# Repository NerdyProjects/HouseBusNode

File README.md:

# Hausbus Spielerei

## Short introduction

This repository holds hardware and software design for a work in progress house bus system.
It operates using a 4-wire bus using the CAN bus as well as supply of ~10 - 20 V.
It should provide a base for very simple nodes (e.g. sensors, digital actors) as well as more complex nodes (e.g. a heating system controller).

## Background

The system design started in November 2017 when the need of a better heating system controller arose in a housing project in Wurzen, Germany.
The gas heating system, a well overpowered Viessmann Atola controlled by a Viessmann Trimatik MC should be better controlled in light load conditions with options to get it better tuned to the actual needs.
A good heating system needs to be remote controllable as well as take a lot of different control inputs, in best case from every room as well as every radiator and maybe even some valves in between.

Additionally, it is nice to gather statistics about used gas, electricity and water.

When such a system is in place already, it would be great to combine it with other actors and sensors around the house: Doorbell, switches, PIR sensors, dimming of lights (without having to use expensive dimmers or even without standing up from your desk).

## Design implications

The design is driven by a mind that likes to play around with technology, gather statistics and try to optimize the world around.
The design is not meant to be used for things that require absolute reliability or fool-saveness.
The design is not meant to be used in applications or environment where security is needed.
The communication between the nodes happen without any security layer: Every node is able to set any value in any other node, so can everybody tapping into the bus wire.

# Hardware description

## PCB Errata

## Mini-PCB

* Triac T1/T2 (Pin 1/2) need to be exchanged. Easiest to be done by soldering Triac backwards just with Pin 1 and 2 and using a wire for Pin 3.

## Microcontroller

The microcontroller in use is the STM32F072RBT6. It is powered by an ARM Cortex-M0 core with 128 kBytes of flash memory and 16 kBytes of SRAM data memory.

### Compatible boards/projects

There is a list of boards using the same controller.
Because of the broad availability and use of these boards, they might be worth a look for application examples (be it hardware or software).

* STM32F072 Discovery Kit
* STM32 Nucleo-64 / Nucleo-F072RB (Arduino like development board)

## BUS

The CAN-Bus is not meant to operate with long stub lines - but using slew rate control, it is safe to do so.
Following CAN physical layer requirements (TI SLLA270, 01/2008), the maximum stub length should be less than 1/3rd of the critical length, which equals the down-and-back delay of the transition time, which is the longer of the rise or fall times:

| HVD230 Rs | Tplh | Tphl | 1/3 of critical length | max. length @ 250 kBaud | max. length @ 125 kBaud |
| --------- | ---- | ---- | ---------------------- | ----------------------- | ----------------------- |
| 0         | 35 ns| 70 ns | 2.3 m (1.1 m)         | ~280 m |
| 10k       | 65 ns| 130 ns | 4.3 m (2.1 m)        | ~282 m |
| 100k      | 500 ns| 870 ns | 29 m (16.6 m) | ~208 m |

The max. length is calculated using the HVD230 given tp of ~37 ns, the comparator delay inside the processor is estimated with 10 ns.
The calculation shows, that the effect of slew rate control on bus length is minimal for these speeds.
At a higher speed, the transition delay inside the driver takes up bigger parts of the available time window, which is ~3 us for 250 kBaud.
Also, it is not exactly clear to me why the speed does not matter when calculating the stub lengths, but the given results clearly show, that 100k slew rate control and a 250 kBaud bus is appropriate for usage in a house.
For a normal sized living house, the bus should be fed through each flats hallway to allow each rooms' connection with stubs.
For houses like the housing project where this is designed for, this leads to a bus length of approximately 120m:
Both ends "stub" 30m each, 2 times 3 floors with 3.5 m height (connection just through stubs, as all points are reachable within 30m), 2 times basement to pass to the next building (15m), which sums up to 30+30+2\*3\*3.5+15+15 = 111m

## Power

Each bus node has an on-board step down converter to convert the bus voltage (because of the availabiliy of cheap step downs <24 V) to 3.3 V for the circuit.
Some applications might use the bus power directly, when exact voltage does not matter and current is limited (so the bus is not powered off).
The network should be usable with ~50 nodes that can be power-fed at multiple times in the bus.

The bus cable resistance following the above approximation (120m) and taking 0.4mm/0.13mm² cable (AWG26) as a worst case candidate comes down to ~30 ohms.
Taking a worst case, default active operational current of 50 mA @ 3.3V for 50 nodes (~8 W), as well as a supply of 18 V already results in a current consumption of 450 mA, which would be too big for the given cabling.
Due to this, power consumption of nodes should be kept in mind when deploying them.

A node that is close to a powerful bus power feed can easily use the bus power to drive lighting or a doorbell with 20 W.
It is left to the deployer of the bus system to ensure that the bus voltage drop is taken into account when deploying powerful nodes.

## Board pin mapping (Board: Hausspielerei 11/2017)

Please always consider the schematics for details.
Still, the following table describes the available connectors, suggested use cases and possible use cases.

### Analog IO

Analog pins on this board are named with their corresponding usage on the Viessmann Trimatik-MC.
All of the pins in the list feature strong pullup resistors, that are all switched by /PA0 (Q1) to AVCC (3,3V)

| pin name | controller pin | available hardware | possible alternative functions |
| -------- | -------------- | ------------------ | ------------------------------ |
| IN\_ATS  | PA1            | series 0805, 2x 0805 to GND | USART2\_RTS / RS422 DE / RS485 DE, USART4\_RX |
| IN\_KTS  | PA2            | 0805 to GND | USART2\_TX / RS422 TX / RS485 TX, COMP1\_INP, COMP2\_INM, COMP2\_OUT |
| IN\_VTS  | PA3            | 0805 to GND | USART2\_RX / RS422 RX / RS485 RX, COMP2\_INP |
| IN\_STS  | PA4            | 0805 to GND | COMP2\_INM, COMP1\_INM, DAC_OUT1 |
| IN\_FB1  | PA5            | 0805 to GND | COMP1\_INM, COMP2\_INM, DAC_OUT2, SPI1\_SCK |  
| IN\_FB2  | PA6            | 0805 to GND | COMP1\_OUT, SPI1\_MISO |
| LED_A    | PA7            | series 0805 | COMP2\_OUT, SPI1\_MOSI |

### Connectors

| Connector  | Pins                           | controller pins | primary purpose | alternative purposes | conflicting with |
| ---------- | -----------------------------  | --------------- | --------------- | -------------------- | ---------------  |
| J12, J13   | VCC GND CANH CANL              |                 | Power (5-24V), bus + passthrough |     | No conflicts |
| SMPS (J3)  | NC Vin(J12/13 Vcc) GND 3,3V    |                 | SMPS module for 3,3V power supply |    | No conflicts |
| RS485 (J17)| GND A B 3,3V                   | PA1, PA2, PA3   | RS485/RS422 connection to sub boards | By bridging appropriate Pins in U1, it can be used as USART2 TX/RX/RTS or Analog inputs | DE: J9 / IN\_ATS |
| J9         | IN\_FB1 3,3V GND IN\_ATS        | PA5, PA1        | digital/analog input for hall sensor module | | IN\_ATS: RS485 DE |
| D1 (LED A) | GND LED\_A                     | PA7             | General purpose LED | IO, Analog comparator output, SPI MOSI | No conflicts |
| J16 (230V) | SW2-A SW2-B SW1-A SW1-B        | PB0 (SW2), PB11 (SW1) | Opto triac + triac controlled power switch for 230V AC | Switching, Dimming, GPIO | No conflicts |
| J6 (DIN4..1) | DIN4 DIN3 DIN2 DIN1          | PB1 PB2 PB10 PF1 | GPIO | DIN4: Analog In | No conflicts |
| D2 (LED B) | GND LED\_B                     | PA15            | General purpose LED | IO, USART2\_RX | No conflicts |
| J5 (GND)   | GND GND GND GND                |                 | | |
| J14        | SW3 GND SW4 GND                | PA8 PB3         | Open drain load switch, TIM1\_CH1, TIM2\_CH2 | 4: SPI1\_SCK | No conflicts |
| J15        | SW1 GND SW2 GND                | PB4 PB5         | Open drain load switch, TIM3\_CH1, TIM3\_CH2 | SPI1\_MISO SPI1\_MOSI | No conflicts |
| J10 (I2C)  | 3,3V GND SCL SDA               | PB6 PB7         | I2C | USART1\_TX, USART1\_RX | Shared I2C bus with J8, EEPROM |
| J8 (I2C)   | 3,3V GND SCL SDA               | PB6 PB7         | I2C | USART1\_TX, USART1\_RX | Shared I2C bus with J10, EEPROM |
| J4 (BOOT)  | GND BOOT 3,3V                  | BOOT            | bootmode selection (1-2: FLASH, 2-3: system rom bootloader) | | |
| J7 (SWD)   | SWDIO SWDCLK GND               | PA13 PA14       | SWD debug / programming connector | | No conflicts |
| J11 (USB)  | DP DM GND                      | PA12 PA11       | USB connection | COMP2\_OUT COMP1\_OUT | No conflicts |
| J18 (UART) | TX RX GND                      | PA9 PA10        | USART1\_TX USART1\_RX | TIM1\_CH2 TIM1\_CH3 | No conflicts |
| J1/J2      | see schematics                 | see schematics  | Viessmann Trimatik MC X1 | use signals individually, see schematics |

A lot of the connectors share the same physical pins.
Especially the Trimatik-MC connector shares pins with almost all other connectors, so it is not explicitly listed in the above table.
Some functionality of the Trimatik-MC might be disabled by cutting pins (or checking for electrical compatibility) - otherwise the following connectors are conflict free here as well:

  * SWD
  * I2C
  * CAN
  * J15 / Open drain switches 1, 2

When keeping minimum Trimatik-MC controller features, following connectors can never be used:
  
  * USB
  * J17 RS422/RS485
  * 230V SW1 (only by cutting J1 Pin12)

Please have a look at the schematics when wanting to use conflicting connectors at the same time, there might be options :-)

# Software description

## USB CAN Adapter firmware
The hardware should be compatible to the [CandleLight](https://github.com/HubertD/candleLight) project, so you can just use the [CandleLight Firmware](https://github.com/HubertD/candleLight_fw).
Just one change: This hardware does not supply any external oscillator, so the firmware might need to be adapted.
This firmware has not been tested.

## Ideas

## RTOS
The simplicity of each individual node does not require an operating system.
For simplicity, ease of use and improval of robustness, a simple task scheduler is highly recommended.

[ChibiOs](http://www.chibios.org) provides a simple, high performance, low footprint kernel (ChibiOS/RT) and a useful hardware abstraction layer (HAL).
Both are well tested for the used Cortex M0 controller.
The HAL provides support for almost all components of the controller:

* USB (including USB-CDC for serial connections)
* GPIO
* ADC (including using DMA transfers)
* CAN
* Timers (including PWM outputs)
* I2C

An introduction document is available: [ChibiOS/RT3.0 The ultimate Guide](http://chibios.org/dokuwiki/doku.php?id=chibios:book:start)

### Encryption / signature
Although not necessary in this project, I am interested in using a crypto library.
http://kmackay.ca/micro-ecc/ seems nice to use on our Cortex M0.

### CAN protocol
  Libuavcan CAN library (Cortex M0: 30 kBytes flash, 6 kBytes ram) seems nice as it supports broadcast messages as well as unicast transfers.

  Its DSL allows building arbitrary messages for different data to transmit.
  All devices need to agree on the subset of packets they want to use (easy, as otherwise they could not use them anyway).

  There is no additional network management layer necessary.

  Tooling seems good, development stable.

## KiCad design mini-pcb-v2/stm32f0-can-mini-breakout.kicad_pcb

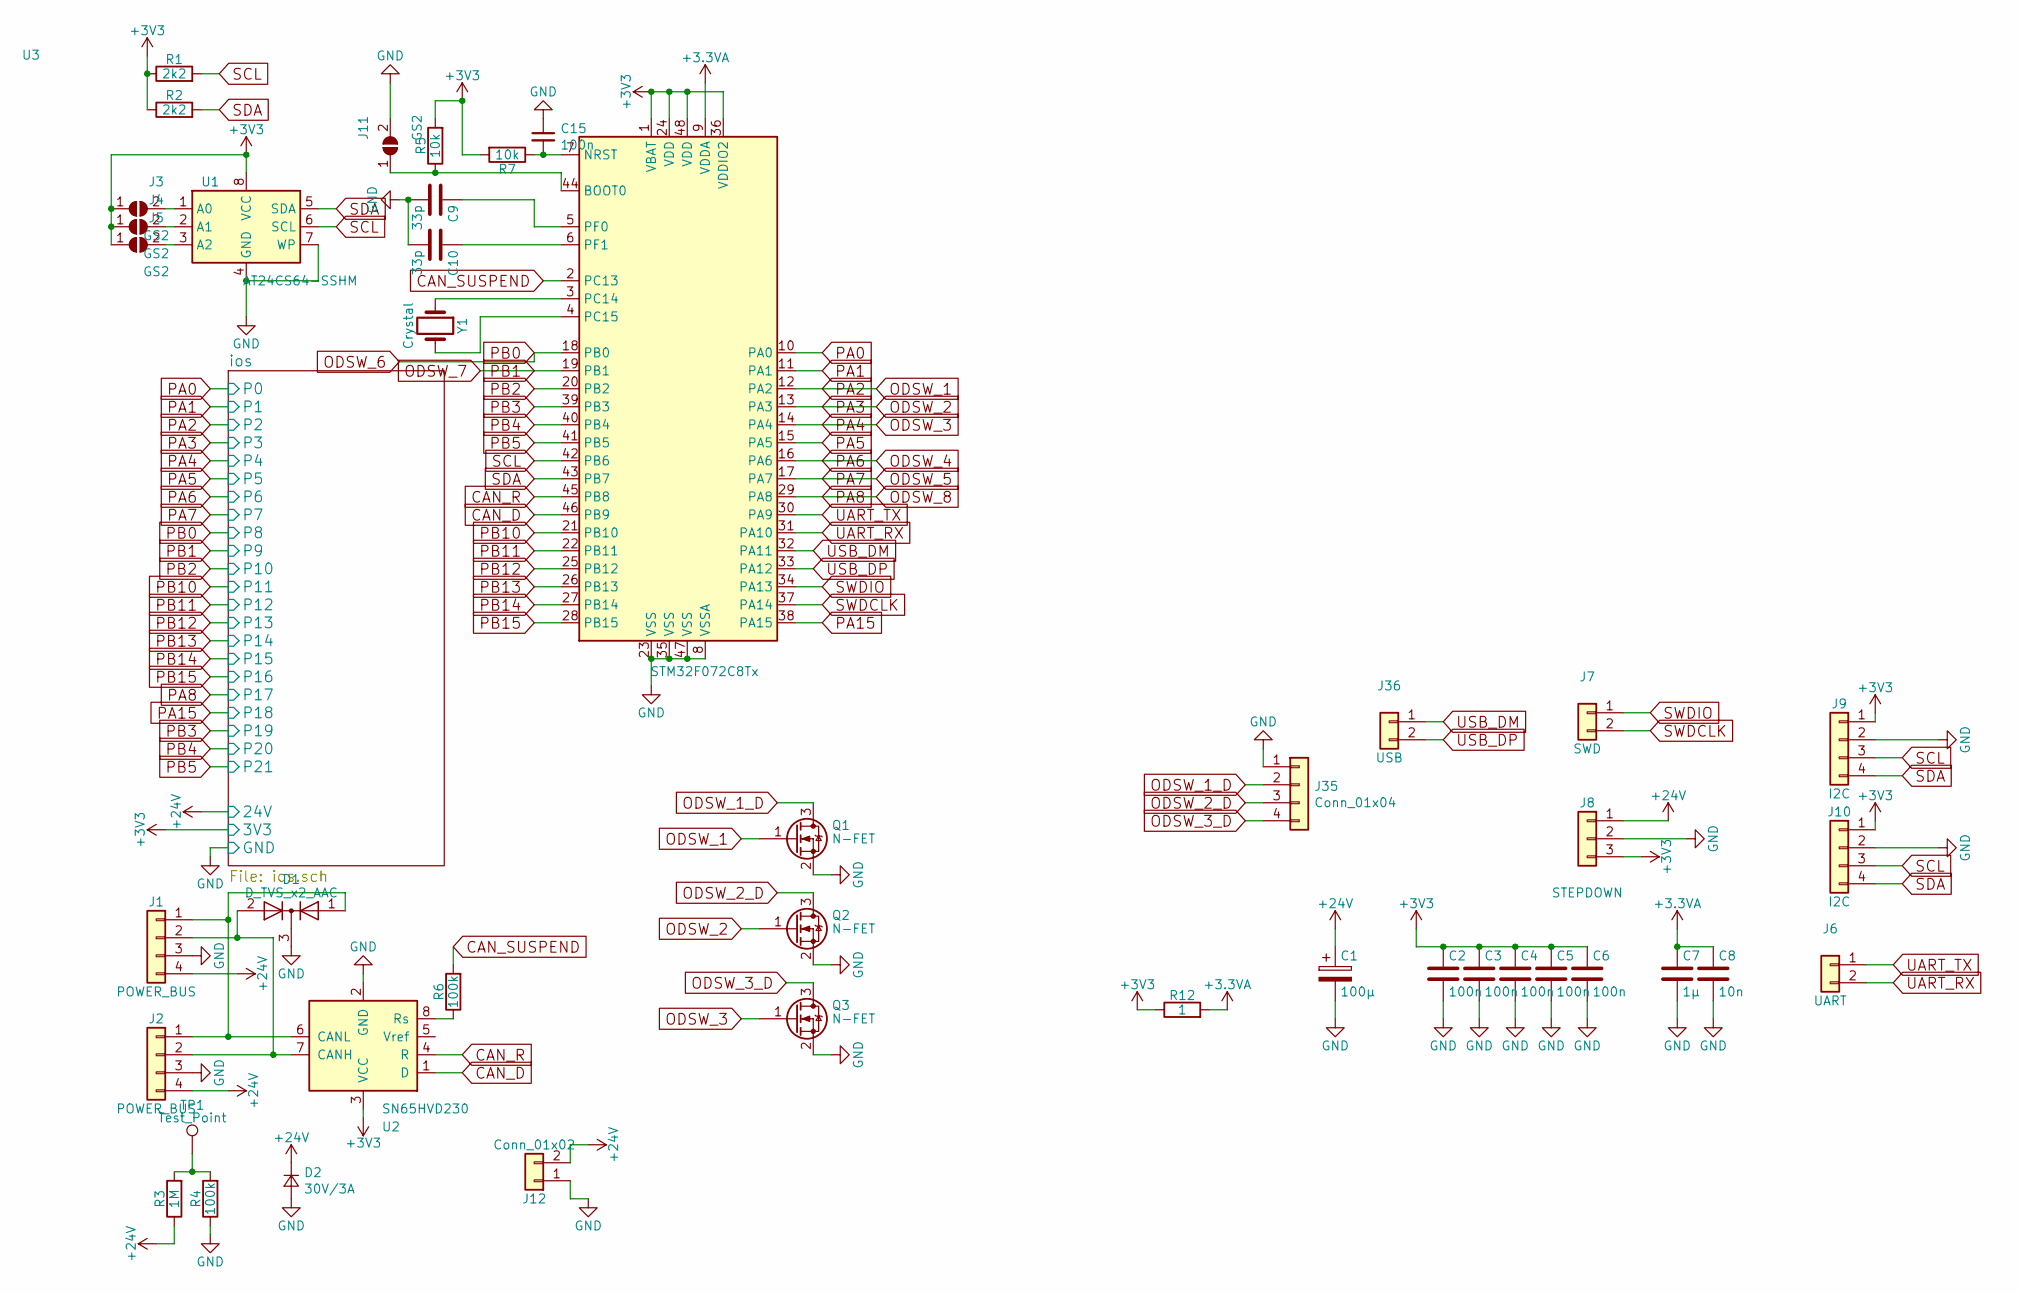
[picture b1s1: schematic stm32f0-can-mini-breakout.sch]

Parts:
C1: 100µ; CP_Radial_D6.3mm_P2.50mm
C2, C3, C4, C5, C6, C15: 100n; C_0603_1608Metric_Pad1.05x0.95mm_HandSolder
C7: 1µ; C_0805_2012Metric_Pad1.15x1.40mm_HandSolder
C8: 10n; C_0603_1608Metric_Pad1.05x0.95mm_HandSolder
C9, C10: 33p; C_0805_2012Metric_Pad1.15x1.40mm_HandSolder
D1: D_TVS_x2_AAC; SOT-23_Handsoldering
D2: 30V/3A; D_SMB
J1, J2: POWER_BUS; JST_XH_B4B-XH-A_1x04_P2.50mm_Vertical
J3, J4, J5: GS2; R_0402_1005Metric
J6: UART; PinHeader_1x02_P2.54mm_Vertical
J7: SWD; PinHeader_1x02_P2.54mm_Vertical
J8: STEPDOWN; PinHeader_1x03_P2.54mm_Vertical
J9, J10: I2C; PinHeader_1x04_P2.54mm_Vertical
J11: GS2; SolderJumper-2_P1.3mm_Open_RoundedPad1.0x1.5mm
J12: Conn_01x02; TerminalBlock_Phoenix_PT-1,5-2-3.5-H_1x02_P3.50mm_Horizontal
J35: Conn_01x04; PinHeader_1x04_P2.54mm_Vertical
J36: USB; PinHeader_1x02_P2.54mm_Vertical
Q1, Q2, Q3: N-FET; SOT-23
R1, R2: 2k2; R_0603_1608Metric_Pad1.05x0.95mm_HandSolder
R3: 1M; R_0805_2012Metric_Pad1.15x1.40mm_HandSolder
R4, R6: 100k; R_0603_1608Metric_Pad1.05x0.95mm_HandSolder
R5, R7: 10k; R_0603_1608Metric_Pad1.05x0.95mm_HandSolder
R12: 1; R_0805_2012Metric_Pad1.15x1.40mm_HandSolder
TP1: Test_Point; Pin_D0.7mm_L6.5mm_W1.8mm_FlatFork
U1: AT24CS64-SSHM; SOIC-8_3.9x4.9mm_P1.27mm
U2: SN65HVD230; SOIC-8_3.9x4.9mm_P1.27mm
U3: STM32F072C8Tx; LQFP-48_7x7mm_P0.5mm
Y1: Crystal; Crystal_C38-LF_D3.0mm_L8.0mm_Vertical

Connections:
+3.3VA: C7.1, C8.1, R12.2, U3.9 (VDDA)
+3V3: C2.1, C3.1, C4.1, C5.1, C6.1, J3.1 (A), J4.1 (A), J5.1 (A), J8.3, J9.1, J10.1, R1.1, R2.1, R5.2, R7.2, R12.1, U1.8 (VCC), U2.3 (VCC), U3.1 (VBAT), U3.24 (VDD), U3.36 (VDDIO2), U3.48 (VDD); also elsewhere on the board
+24V: C1.1, D2.1 (K), J1.4, J2.4, J8.1, J12.2, R3.1; also elsewhere on the board
CAN_D: U2.1 (D), U3.46 (PB9)
CAN_R: U2.4 (R), U3.45 (PB8)
CAN_SUSPEND: R6.2, U3.2 (PC13)
GND: C1.2, C2.2, C3.2, C4.2, C5.2, C6.2, C7.2, C8.2, C9.2, C10.2, C15.1, D1.3 (K), D2.2 (A), J1.3, J2.3, J8.2, J9.2, J10.2, J11.2 (B), J12.1, J35.1, Q1.2 (S), Q2.2 (S), Q3.2 (S), R4.1, U1.4 (GND), U1.7 (WP), U2.2 (GND), U3.8 (VSSA), U3.23 (VSS), U3.35 (VSS), U3.47 (VSS); also elsewhere on the board
unnamed: C9.1, U3.5 (PF0)
unnamed: C10.1, U3.6 (PF1)
unnamed: C15.2, R7.1, U3.7 (NRST)
unnamed: D1.1 (A), J1.1, J2.1, U2.6 (CANL)
unnamed: D1.2 (A), J1.2, J2.2, U2.7 (CANH)
unnamed: J3.2 (B), U1.1 (A0)
unnamed: J4.2 (B), U1.2 (A1)
unnamed: J5.2 (B), U1.3 (A2)
unnamed: J11.1 (A), R5.1, U3.44 (BOOT0)
unnamed: R3.2, R4.2, TP1.1
unnamed: R6.1, U2.8 (Rs)
unnamed: U3.3 (PC14), Y1.1
unnamed: U3.4 (PC15), Y1.2
ODSW_1: Q1.1 (G), U3.12 (PA2); also elsewhere on the board
ODSW_1_D: J35.2, Q1.3 (D)
ODSW_2: Q2.1 (G), U3.13 (PA3); also elsewhere on the board
ODSW_2_D: J35.3, Q2.3 (D)
ODSW_3: Q3.1 (G), U3.14 (PA4); also elsewhere on the board
ODSW_3_D: J35.4, Q3.3 (D)
ODSW_4: U3.16 (PA6); also elsewhere on the board
ODSW_5: U3.17 (PA7); also elsewhere on the board
ODSW_6: U3.18 (PB0); also elsewhere on the board
ODSW_7: U3.19 (PB1); also elsewhere on the board
ODSW_8: U3.29 (PA8); also elsewhere on the board
PA0: U3.10 (PA0); also elsewhere on the board
PA1: U3.11 (PA1); also elsewhere on the board
PA5: U3.15 (PA5); also elsewhere on the board
PA15: U3.38 (PA15); also elsewhere on the board
PB2: U3.20 (PB2); also elsewhere on the board
PB3: U3.39 (PB3); also elsewhere on the board
PB4: U3.40 (PB4); also elsewhere on the board
PB5: U3.41 (PB5); also elsewhere on the board
PB10: U3.21 (PB10); also elsewhere on the board
PB11: U3.22 (PB11); also elsewhere on the board
PB12: U3.25 (PB12); also elsewhere on the board
PB13: U3.26 (PB13); also elsewhere on the board
PB14: U3.27 (PB14); also elsewhere on the board
PB15: U3.28 (PB15); also elsewhere on the board
SCL: J9.3, J10.3, R1.2, U1.6 (SCL), U3.42 (PB6)
SDA: J9.4, J10.4, R2.2, U1.5 (SDA), U3.43 (PB7)
SWDCLK: J7.2, U3.37 (PA14)
SWDIO: J7.1, U3.34 (PA13)
UART_RX: J6.2, U3.31 (PA10)
UART_TX: J6.1, U3.30 (PA9)
USB_DM: J36.1, U3.32 (PA11)
USB_DP: J36.2, U3.33 (PA12)

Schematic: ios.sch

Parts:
C11, C12, C13, C14: 33n; C_Rect_L18.0mm_W6.0mm_P15.00mm_FKS3_FKP3
J13, J14, J15, J16, J17, J18, J26, J27, J28, J30, J31, J32, J33, J37, J38: Conn_01x09; Pin_Header_Straight_1x09_Pitch2.54mm
J19, J20, J21: Conn_01x08; Pin_Header_Straight_1x08_Pitch2.54mm
J22, J23, J24, J25, J39, J40, J43, J44, J45: Conn_01x05; Pin_Header_Straight_1x05_Pitch2.54mm
J29, J34, J41: Conn_01x07; Pin_Header_Straight_1x07_Pitch2.54mm
J46, J47, J48, J49: Screw_Terminal_01x02; TerminalBlock_Phoenix_PT-3.5mm_2pol
Q9, Q10, Q11, Q12: BT138-800; TO-220_Neutral123_Vertical
R13, R15, R17, R19: 360; R_0805
R14, R16, R18, R20: 330; R_0805
R21, R22, R23, R24: 66; R_Axial_DIN0207_L6.3mm_D2.5mm_P15.24mm_Horizontal
RV1, RV2, RV3, RV4: Varistor; RV_Disc_D15.5_W4.2_P7.5
U4, U5, U6, U7: MOC3063M; DIP-6_W7.62mm

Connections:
+3V3: J27.1, J27.2, J27.3, J27.4, J27.5, J27.6, J27.7, J27.8, J27.9; also elsewhere on the board
+24V: J37.1, J37.2, J37.3, J37.4, J37.5, J37.6, J37.7, J37.8, J37.9; also elsewhere on the board
GND: J25.1, J25.2, J25.3, J25.4, J25.5, J29.1, J38.1, J38.2, J38.3, J38.4, J38.5, J38.6, J38.7, J38.8, J38.9, U4.2, U5.2, U6.2, U7.2; also elsewhere on the board
unnamed: C11.1, R21.2
unnamed: C11.2, J46.1, Q9.1 (A1), R14.1, RV1.2
unnamed: C12.1, R22.2
unnamed: C12.2, J47.1, Q10.1 (A1), R16.1, RV2.2
unnamed: C13.1, J48.2, Q11.1 (A1), R20.1, RV3.2
unnamed: C13.2, R23.2
unnamed: C14.1, J49.2, Q12.1 (A1), R18.1, RV4.2
unnamed: C14.2, R24.2
unnamed: J46.2, Q9.2 (A2), R13.1, R21.1, RV1.1
unnamed: J47.2, Q10.2 (A2), R15.1, R22.1, RV2.1
unnamed: J48.1, Q11.2 (A2), R19.1, R23.1, RV3.1
unnamed: J49.1, Q12.2 (A2), R17.1, R24.1, RV4.1
unnamed: Q9.3 (G), R14.2, U4.4
unnamed: Q10.3 (G), R16.2, U5.4
unnamed: Q11.3 (G), R20.2, U7.4
unnamed: Q12.3 (G), R18.2, U6.4
unnamed: R13.2, U4.6
unnamed: R15.2, U5.6
unnamed: R17.2, U6.6
unnamed: R19.2, U7.6
ODSW_1: J15.1; also elsewhere on the board
ODSW_2: J16.1; also elsewhere on the board
ODSW_3: J17.1; also elsewhere on the board
ODSW_4: J19.2; also elsewhere on the board
ODSW_5: J19.1; also elsewhere on the board
ODSW_6: J20.2; also elsewhere on the board
ODSW_7: J20.1; also elsewhere on the board
ODSW_8: J30.1; also elsewhere on the board
PA0: J13.1; also elsewhere on the board
PA1: J14.1; also elsewhere on the board
PA5: J18.1; also elsewhere on the board
PA15: J31.1; also elsewhere on the board
PB2: J21.1; also elsewhere on the board
PB3: J32.1; also elsewhere on the board
PB4: J33.1; also elsewhere on the board
PB5: J33.2; also elsewhere on the board
PB10: J22.1; also elsewhere on the board
PB11: J23.1; also elsewhere on the board
PB12: J26.2; also elsewhere on the board
PB13: J26.1; also elsewhere on the board
PB14: J28.2; also elsewhere on the board
PB15: J28.1; also elsewhere on the board

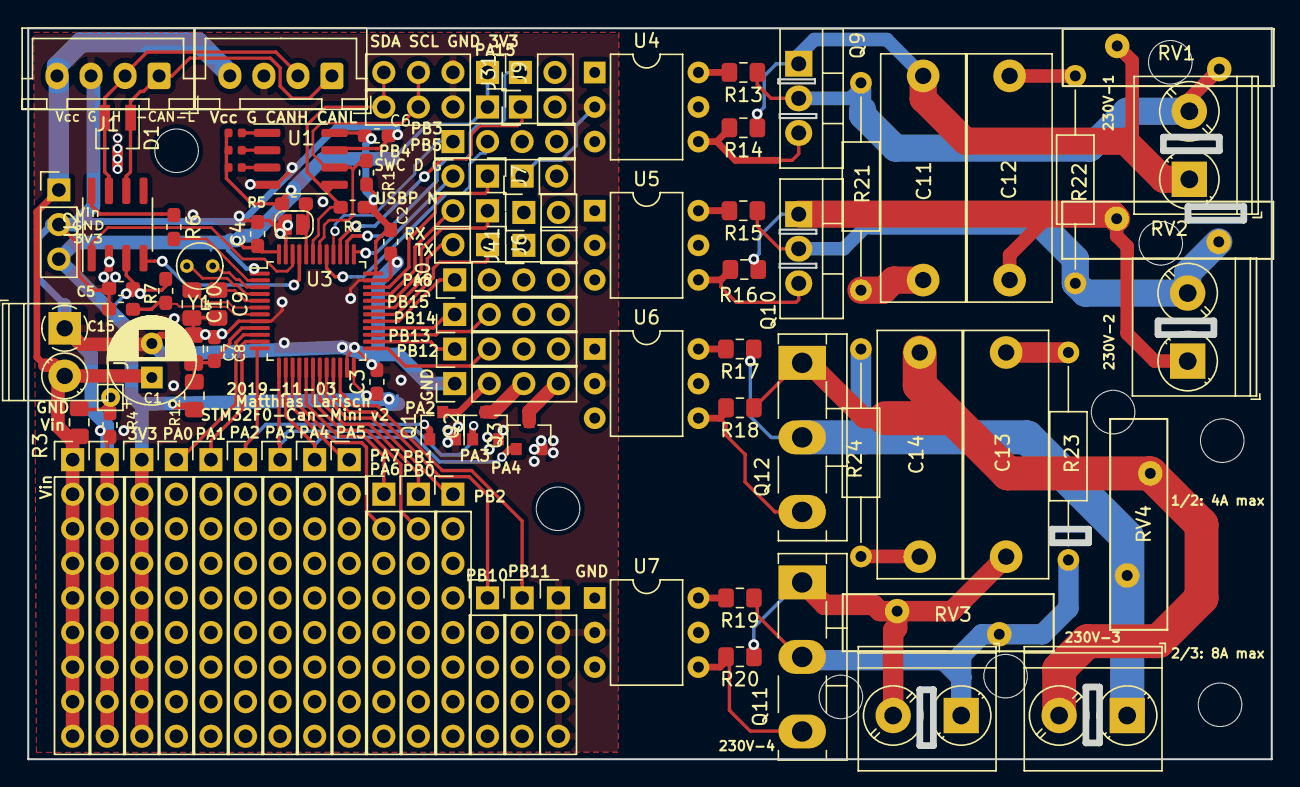
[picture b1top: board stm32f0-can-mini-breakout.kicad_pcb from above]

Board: 2 copper layers, 91.0 x 53.3 mm, 99 parts (1 on the bottom side), 73 nets.

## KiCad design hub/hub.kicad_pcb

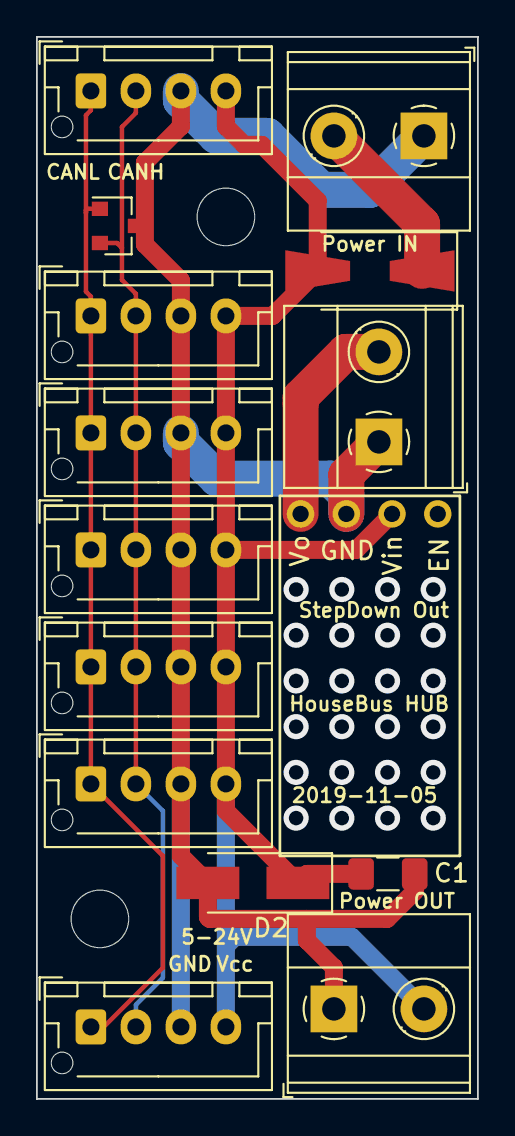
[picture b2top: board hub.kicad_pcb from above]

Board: 2 copper layers, 24.5 x 59.0 mm, 17 parts (0 on the bottom side), 6 nets.

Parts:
C1: 10µ; C_1206_3216Metric_Pad1.42x1.75mm_HandSolder
D1: SK34; D_SMA-SMB_Universal_Handsoldering
D2: D_TVS; D_SMA_Handsoldering
D3: D_TVS_x2_AAC; SOT-23
H1, H2: MountingHole; MountingHole_3.2mm_M3
J1, J2, J3, J4, J5, J6, J9: Conn_01x04; JST_XH_B4B-XH-AM_1x04_P2.50mm_Vertical
J7: Power IN; TerminalBlock_Phoenix_MKDS-1,5-2_1x02_P5.00mm_Horizontal
J8, J10: Power OUT; TerminalBlock_Phoenix_MKDS-1,5-2_1x02_P5.00mm_Horizontal
U1: MP2315-Mini-Module; MP2315-Mini

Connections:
CANH: D3.2, J1.2, J2.2, J3.2, J4.2, J5.2, J6.2, J9.2
CANL: D3.1, J1.1, J2.1, J3.1, J4.1, J5.1, J6.1, J9.1
GND: C1.2, D2.2, D3.3, J1.3, J2.3, J3.3, J4.3, J5.3, J6.3, J7.1, J8.1, J9.3, J10.1, U1.2
unnamed: D1.1, J7.2
unnamed: J10.2, U1.1
VCC: C1.1, D1.2, D2.1, J1.4, J2.4, J3.4, J4.4, J5.4, J6.4, J8.2, J9.4, U1.3

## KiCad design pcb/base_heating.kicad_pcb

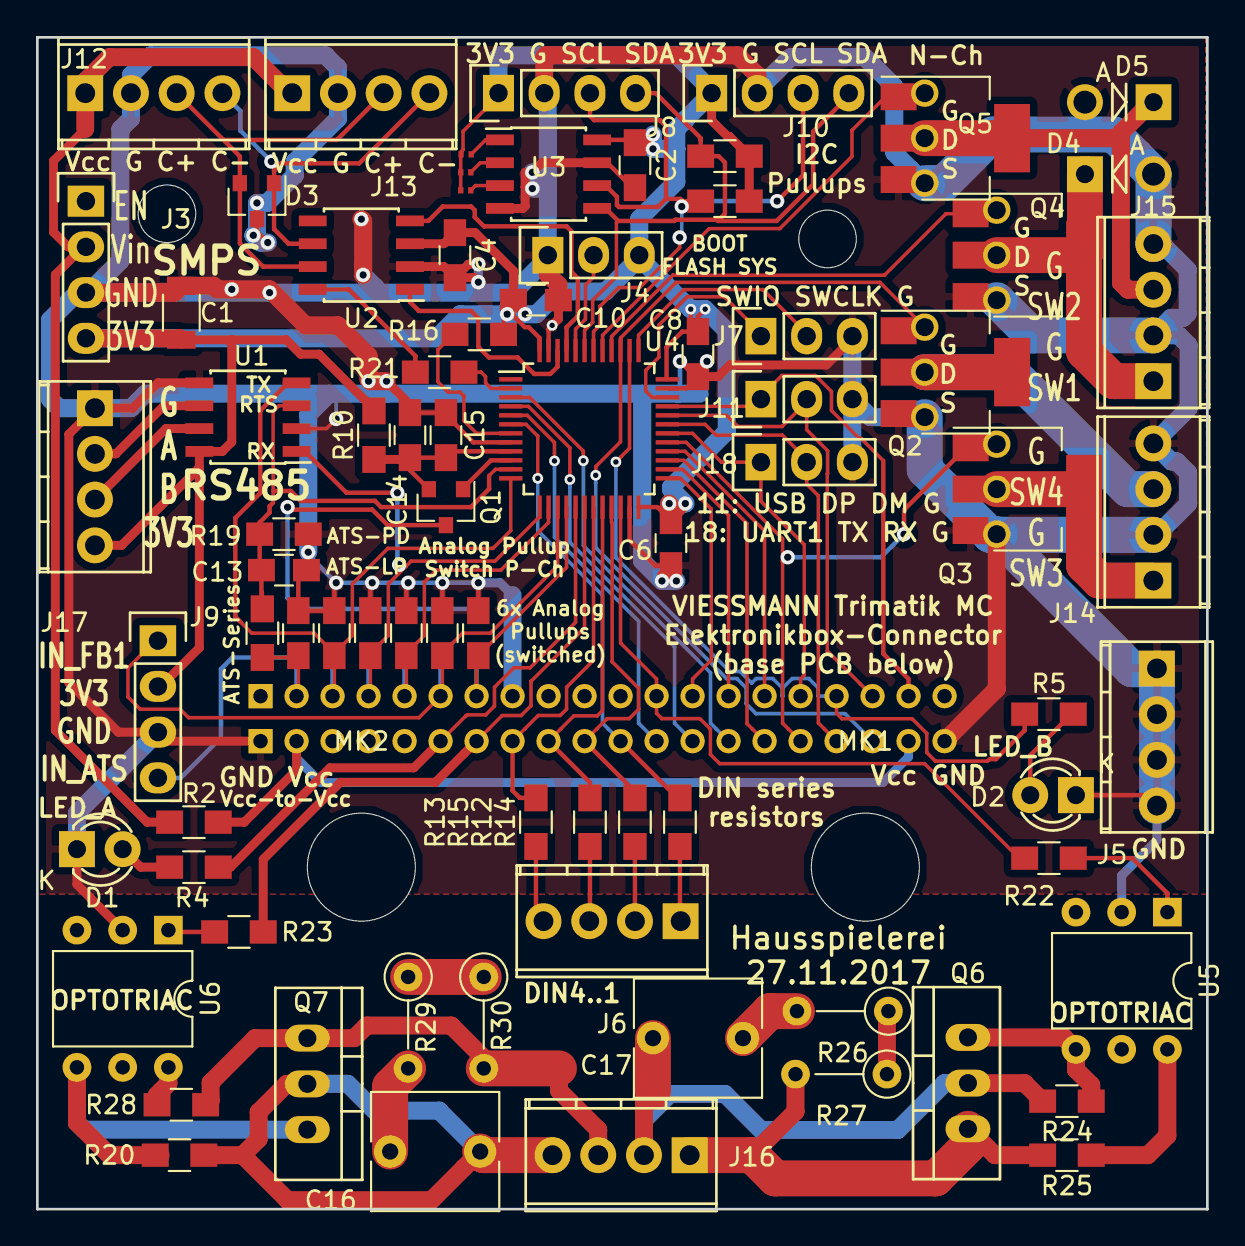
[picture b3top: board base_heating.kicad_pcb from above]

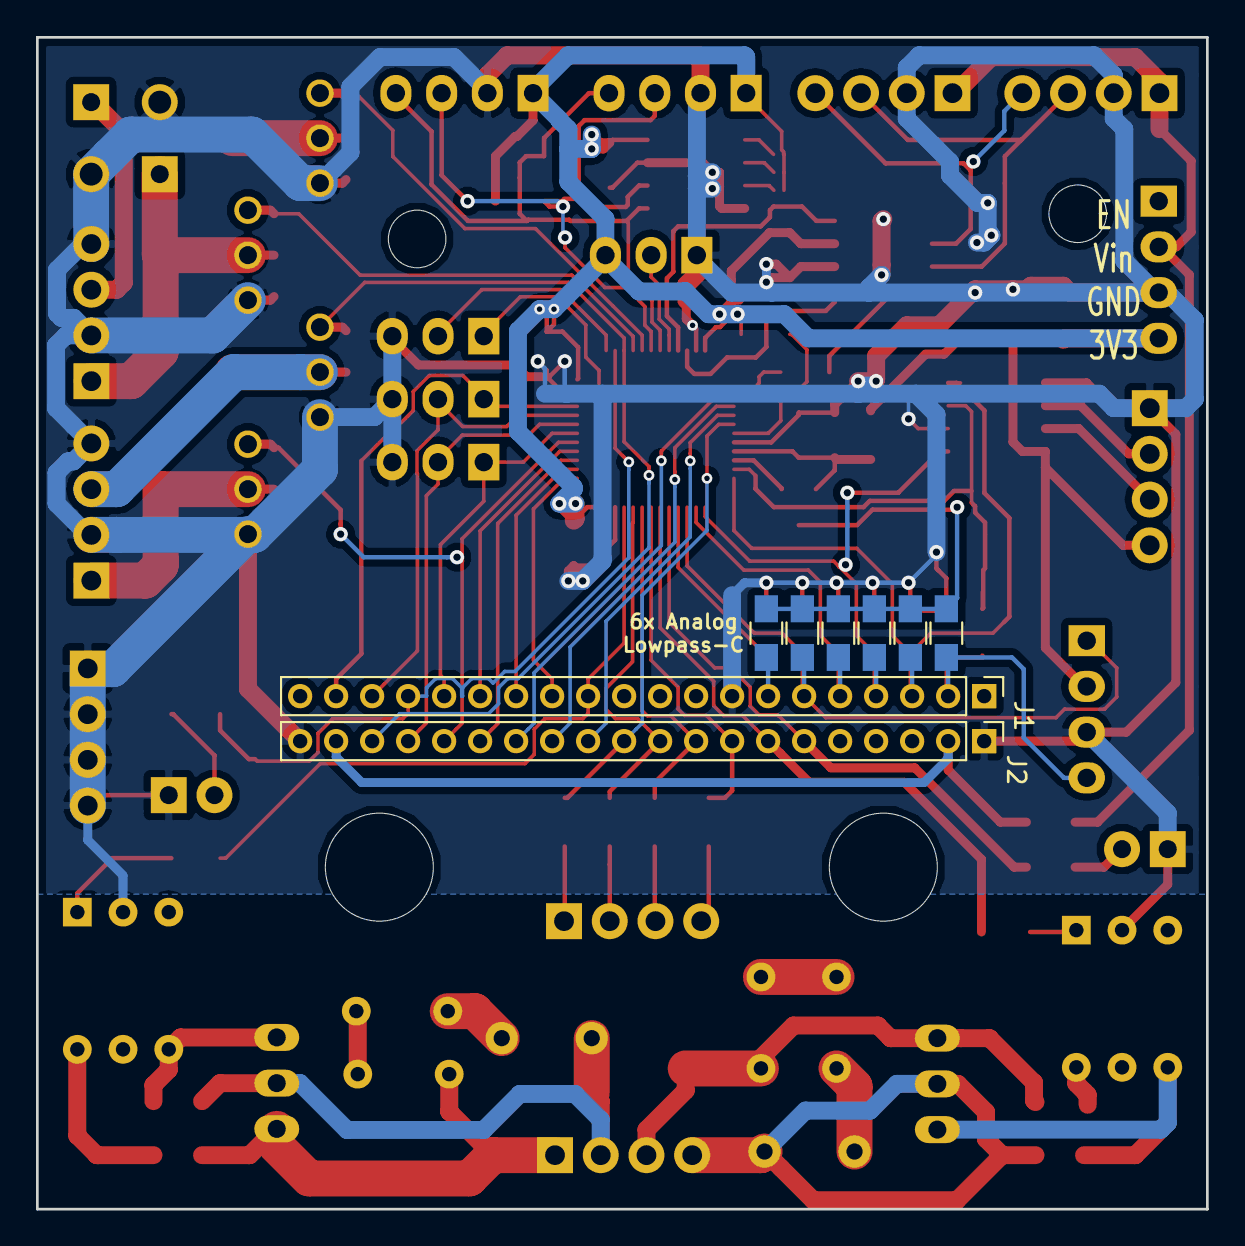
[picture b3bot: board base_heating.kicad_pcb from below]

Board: 2 copper layers, 65.0 x 65.1 mm, 88 parts (8 on the bottom side), 78 nets.

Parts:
C1: 10µ; C_1206
C2, C3, C4, C5, C6, C7, C8, C9, C10, C11, C12, C13: 100n; C_0805_HandSoldering
C14: 1µ; C_0805_HandSoldering
C15: 10n; C_0805_HandSoldering
C16, C17: 10n; C_Rect_L7.0mm_W6.5mm_P5.00mm
D1, D2: LED; LED-3MM
D3: D_TVS_x2_AAC; SOT-23
D4, D5: D_Zener; Diode_DO-41_SOD81_Vertical_AnodeUp
J1: X1_1-20; Pin_Header_Straight_1x20_Pitch2.00mm
J2: X1_21-40; Pin_Header_Straight_1x20_Pitch2.00mm
J3: STEPDOWN; Pin_Header_Straight_1x04
J4: BOOT; Pin_Header_Straight_1x03
J5: GND; TerminalBlock_Pheonix_MPT-2.54mm_4pol
J6: DIN_1; TerminalBlock_Pheonix_MPT-2.54mm_4pol
J7: SWD; Pin_Header_Straight_1x03
J8, J10: I2C; Pin_Header_Straight_1x04
J9: A_D_IN; Pin_Header_Straight_1x04
J11: USB; Pin_Header_Straight_1x03
J12, J13: POWER_BUS; TerminalBlock_Pheonix_MPT-2.54mm_4pol
J14: DCSW_2; TerminalBlock_Pheonix_MPT-2.54mm_4pol
J15: DCSW_1; TerminalBlock_Pheonix_MPT-2.54mm_4pol
J16: ACSW_1; TerminalBlock_Pheonix_MPT-2.54mm_4pol
J17: RS422; TerminalBlock_Pheonix_MPT-2.54mm_4pol
J18: UART_1; Pin_Header_Straight_1x03
JP1, JP2, JP3: Jumper_NO_Small; C_0201_NoSilk
MK1, MK2: Mounting_Hole; MountingHole_6mm
Q1: NTR2101P; SOT-23
Q2, Q3, Q4, Q5: IRF540N; SOT-223-3_TabPin2
Q6, Q7: BT136; TO-220_Neutral123_Vertical
R1, R3, R6, R8, R9, R11: 500; R_0805_HandSoldering
R2: 0; R_0805_HandSoldering
R4, R5: 120; R_0805_HandSoldering
R7, R12, R13, R14, R15, R16, R19: 10k; R_0805_HandSoldering
R10: 2; R_0805_HandSoldering
R17, R18: 2k2; R_0805_HandSoldering
R20, R24, R25, R28: 360; R_0805_HandSoldering
R21: 47k; R_0805_HandSoldering
R22, R23: 100; R_0805_HandSoldering
R26, R27, R29, R30: 38; R_Axial_DIN0207_L6.3mm_D2.5mm_P5.08mm_Vertical
U1: MAX3078E; SOIC-8_3.9x4.9mm_Pitch1.27mm
U2: SN65HVD230; SOIC-8_3.9x4.9mm_Pitch1.27mm
U3: AT24CS64-SSHM; SOIC-8_3.9x4.9mm_Pitch1.27mm
U4: STM32F072C8Tx; LQFP-48_7x7mm_Pitch0.5mm
U5, U6: MOC3061M; DIP-6_W7.62mm

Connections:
+3.3VA: C14.1, C15.1, Q1.2, R10.1, U4.9
+3V3: C1.1, C2.1, C4.1, C6.1, C8.1, C10.1, J3.4, J4.3, J8.1, J9.2, J10.1, J17.4, JP1.1, JP2.1, JP3.1, R10.2, R16.1, R17.1, R18.1, U1.8, U2.3, U3.8, U4.24, U4.36, U4.48
+24V: J3.2, J12.1, J13.1, R2.1
/A_PU_ON: Q1.1, U4.10
ACSW_1: J1.12, R22.1, U4.22
ACSW_2: J2.7, R23.1, U4.18
AIN_ATS: C13.1, R7.1, R19.2, U1.3, U4.11
AIN_A_D: C3.1, J1.2, J9.4, R1.2, R7.2
AIN_FB1: C11.1, J1.6, J9.1, R9.2, U4.15
AIN_FB2: C12.1, J1.7, R11.2, U4.16
AIN_KTS: C5.1, J1.3, R3.2, U1.4, U4.12
AIN_STS: C9.1, J1.5, R8.2, U4.14
AIN_VTS: C7.1, J1.4, R6.2, U1.1, U4.13
CAND: U2.1, U4.46
CANH: D3.2, J12.3, J13.3, U2.7
CANL: D3.1, J12.4, J13.4, U2.6
CANR: U2.4, U4.45
CAN_SUSPEND: R21.1, U4.2
DIN1: J2.11, R14.2, U4.6
DIN2: J2.10, R12.2, U4.21
DIN3: J2.9, R15.2, U4.20
DIN4: J2.8, R13.2, U4.19
DIN_SW_B0_135: J2.15, U4.27
DIN_SW_B0_246: J2.14, U4.3
DIN_SW_B1_135: J2.16, Q3.1, U4.29
DIN_SW_B1_246: J2.13, U4.4
DIN_SW_B2_135: J2.17, J18.2, U4.31
DIN_SW_B2_246: J2.12, U4.5
DIN_SW_B3_135: J2.18, Q2.1, U4.39
DOUT_K1_FIRE: J1.19, J11.1, U4.33
DOUT_K2_20A: J1.18, J11.2, U4.32
DOUT_K3_21: J1.14, U4.26
DOUT_K4_T2: J1.16, J18.1, U4.30
DOUT_K5_S3: J1.15, U4.28
DOUT_K6_20B: J1.17, R5.1, U4.38
DOUT_LED_RED: J2.6, R4.1, U4.17
DOUT_SW_UKN: J1.13, U4.25
GND: C1.2, C2.2, C3.2, C4.2, C5.2, C6.2, C7.2, C8.2, C9.2, C10.2, C11.2, C12.2, C13.2, C14.2, C15.2, D1.1, D2.1, D3.3, D4.2, D5.2, J1.8, J2.1, J2.20, J3.3, J4.1, J5.1, J5.2, J5.3, J5.4, J7.3, J8.2, J9.3, J10.2, J11.3, J12.2, J13.2, J14.2, J14.4, J15.2, J15.4, J17.1, J18.3, Q2.3, Q3.3, Q4.3, Q5.3, R19.1, U1.2, U1.5, U2.2, U3.4, U3.7, U4.8, U4.23, U4.35, U4.47, U5.2, U6.2
unnamed: C16.1, J16.4, Q7.2, R20.2
unnamed: C16.2, R29.2
unnamed: C17.1, J16.2, Q6.2, R24.2
unnamed: C17.2, R26.2
unnamed: D1.2, R4.2
unnamed: D2.2, R5.2
unnamed: D4.1, J15.1, Q4.2
unnamed: D5.1, J15.3, Q5.2
unnamed: J4.2, U4.44
unnamed: J6.1, R14.1
unnamed: J6.2, R12.1
unnamed: J6.3, R15.1
unnamed: J6.4, R13.1
unnamed: J14.1, Q3.2
unnamed: J14.3, Q2.2
unnamed: J16.1, Q6.1, R25.2, R27.2
unnamed: J16.3, Q7.1, R28.1, R30.2
unnamed: J17.2, U1.6
unnamed: J17.3, U1.7
unnamed: JP1.2, U3.3
unnamed: JP2.2, U3.2
unnamed: JP3.2, U3.1
unnamed: Q1.3, R1.1, R3.1, R6.1, R8.1, R9.1, R11.1
unnamed: Q6.3, R24.1, U5.4
unnamed: Q7.3, R20.1, U6.4
unnamed: R16.2, U4.7
unnamed: R21.2, U2.8
unnamed: R22.2, U5.1
unnamed: R23.2, U6.1
unnamed: R25.1, U5.6
unnamed: R26.1, R27.1
unnamed: R28.2, U6.6
unnamed: R29.1, R30.1
ODSW_1: Q4.1, U4.40
ODSW_2: Q5.1, U4.41
SCL: J8.3, J10.3, R17.2, U3.6, U4.42
SDA: J8.4, J10.4, R18.2, U3.5, U4.43
SWDCLK: J7.2, U4.37
SWDIO: J7.1, U4.34
VCC_18: J2.2, J2.19, R2.2

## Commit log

2017-11-24 Initial commit
    schematics design/pcb is preliminary POC to discuss the concept
2017-11-27 Finished schematics, updated screenshot
2017-11-27 Create new readme describing the system. WIP
2017-11-27 Add software thoughts
2017-11-28 Update PCB to fabricated version
2017-11-28 Document pin assignments and some software ideas
2017-11-29 fix table layout
2017-11-29 Nicify readme layout
2017-12-03 Add STM32F072 Example as base code
2017-12-03 Add gitignore
2017-12-03 Update hal configuration to hardware capabilities
2017-12-03 Add customized board configuration based on NUCLEO
2017-12-03 Fix main using removed module
2017-12-03 Add libuavcan
    Needs some patches to work with our controller
2017-12-04 Update libuavcan for STM32F0XX
2017-12-04 Fix readme layout
2017-12-12 Add references to CandleLight project
2018-01-13 WIP libuavcan/chibios
2018-01-13 Add chibios stm32f072 demo
2018-01-13 WIP C++ approach
2018-01-13 Add libcanard/chibios as submodules
2018-01-13 update gitignore
2018-01-13 Unix line endings, chibios tunes
2018-01-13 Add board definition, build libcanard
2018-01-13 Basic system compilable
2018-01-14 Correctly enable CAN driver, increase buffers
    This is the first version that was actually observed working on the
    hardware.
2018-01-14 Remove old firmware approach
2018-01-21 smaller base node firmware
2018-01-22 Fix process stack too small
2018-01-22 Let other modules use canard instance
2018-01-22 Simpler microsecond timing for can frames
2018-01-22 Add BME280 environment sensor
2018-01-22 Use ChibiOs CAN driver instead of canard_stm32
2018-01-23 different fixes
2018-01-23 Add flash erase/program driver
2018-01-23 Use CAN thread for sending all messages
2018-01-23 Boilerplate for conditionally be a bootloader
2018-01-23 Implement watchdog and restart request
2018-01-24 Linker file draft for app/bootloader targets
2018-01-24 Add linker scripts, started firmware_update module
2018-01-24 Add DSDL definition
2018-01-24 EEPROM driver, i2c fixes
2018-01-26 EEPROM, configuration storage and editing
2018-01-27 Bootloader boot to application
2018-01-27 Fix I2C initialization and EEPROM write
2018-01-27 Fix eeprom write only once
2018-01-28 various fixes
    more debugging,
    do not fail on broken EEPROM content
    This bootloader has been successfully used on a bunch of boards
2018-01-29 Add valid flags to Environment dsdl
2018-01-29 Read analog inputs, broadcast temperature
2018-01-29 Further optimize environment DSDL
2018-01-29 Enable WFI idle for power saving
2018-01-29 Fix buffer overflow
2018-01-30 WIP pump control
2018-01-30 WIP conduction sensor driver
    Also include qfplib for floating point and refactor analog driver
2018-01-30 fix initialization/bme280
2018-02-01 Multithread canard RX/TX, cleanup conduction sensor
2018-02-03 Implementet pump and conduction sensor
    This version is running (as of now) on the grey water buffer and
    confirmed working pump control :)
2018-02-03 Implement eventcount system
    Count slow, external events (like water/gas counter pulses)
2018-03-12 Add eventcount module
2018-03-12 Add Minipcb
2018-03-12 update dsdl
2018-03-12 update pcb
2018-03-15 Support multiple event count modules
2018-03-15 Allow eventcount work without debounce
2018-03-22 Add BMP280 support
2018-04-02 Conduction sensor threshold for aged sensors
2018-04-03 Add simple SML prefix parsing
2018-04-09 fix baudrate for sml
2018-04-09 Add meter dsdl
2018-04-09 add debug method
2018-04-11 Parse all SML obis messages
2018-04-11 Cleanup sml parsing
2018-04-11 Proper sign handling in SML integers
2018-04-11 finally get SML sign extension/typing right
2018-04-13 ignore generated files
2018-04-13 ignore vendor dir
2018-04-13 untested pump receiver
2018-04-13 add basic dimmer component
2018-04-13 fix sign extension when creating SML packet
2018-04-13 Add PWM driver as framework for light controller
2018-04-14 fix & improve pumpreceiver
2018-04-14 Fix bootloader compilation, increase application flash size
2018-04-14 update conduction sensor threshold
2018-04-14 Initialize PWM pins
2018-04-18 Add more staircase lights
2018-04-18 temporary pullup for dimmer testing
2018-04-18 add hour-based light control
2018-04-18 upgrade ChibiOS to 18.2
2018-04-20 improve pwm spectrum & brightness
2018-04-20 Fix motion sensor, FadeIn on hallway
2018-04-21 preliminary light upgrade
2018-04-22 fix motion sensor timing & fading
2018-04-22 improve animation
2018-04-22 rename some variables
2018-04-26 refactor water refill module
2018-04-27 fix time_data code
2018-04-28 slow down animation
2018-05-03 some more light stuff
2018-05-03 enable light switch
    does not work yet, have to find correct input pin
2018-05-04 disable hallway switch again
2018-05-16 add new greywater pump control
2018-05-23 improve refill behavior
2018-05-28 make conduction sensor more sensitive
    pump PWM does not work for unknown reason, is always on. so it now switches to refill only when it detects that the bottom tank is empty
2018-05-30 pump: remove PWM, add slow IIR and hysteresis
2018-05-30 update hysteresis levels
2018-05-30 adjust levels
2018-06-01 add greywater cooldown
2018-06-02 just some experiments
2018-09-07 Update Chibios to 18.2.2
    also reflect changes for chconf.h
2018-09-07 Sync DSDL files
2018-09-07 triac pcb errata
2018-09-08 Split applications into nodes
    Do not try to run same code on all nodes anymore.
    A node now can have the methods
    app_init
    app_tick
    app_fast_tick
    and should be conditionally compiled via define NODE_NODENAME.
2018-09-08 Initial viessmann_trimatik node
    just debugs keys and temperatures
2018-09-08 Fix analog input pullups, analog filter reset
2018-09-08 Fix key handling, test burner/circulation
2018-09-08 Enable nodes macro in IDE
2018-09-08 Update kicad board
2018-10-20 add more PT500 measurements and key definitions
2018-10-20 Add heating status type and debug broadcast
2018-10-24 better rounding in analog filter
2018-10-24 Include basic heating curve calculation
    WIP intermediate conversions not yet implemented/right
2018-11-04 implement basic heating control
2018-11-04 Update pt500 coefficients
2018-11-06 Add more configuration, actual burner logging
2018-11-09 Implement burner stop, low load detection
2018-11-11 Use also circulation running time for controller
2018-11-11 Further split up modules
    Using a makefile parameter now to compile for individual nodes.
2018-11-11 Implement heating times
    currently, just two different times can be used by defining start/end
    times and relative temperature offsets.
2018-11-20 Style fixes
2018-11-20 Modularize further
    This removes unused modules from being compiled,
    adds a "static dynamic" module registration for incoming transfers
    (WIP - transfer_registrations.h needs to be generated via grep at
    compile time)
    and makes this functionality work with modularized nodes.
    For SML and the default node, transfer_registrations.h have to be
2018-11-21 Cycle extension as flow temperature optimisation
2018-11-21 Fix heating system starting with burner stop phase
2018-11-25 Heating node: try to match target flow better
2018-11-25 Split bootloader into separate application
2018-11-25 Update libcanard
2018-11-28 Bathroom node description
2018-11-30 Refactor BME280 application
2018-11-30 Add humidity alarm/tone node
2018-11-30 Implement bathroom fan control
    first implementation of dew point / wall condensation detection.
    To be abstracted and reused :-)
2018-11-30 fix blinkLed
2018-11-30 Fix bathroom statemachine and blinking
2018-11-30 Better privacy state handling
2018-12-01 Enable fan control, better timeouts for occupancy
2018-12-01 Fix mistake on switching fan pins
2018-12-06 Modularize further, changes to fan/door handling
2018-12-09 Extract dew point related methods for humid. alarm
2018-12-09 Add auto generated DSDL headers from canard dsdlc
2018-12-09 Implement bathroom status broadcast
2019-01-08 fix bathroom status
2019-01-08 Light switch implementation
2019-01-09 implement basic bright light
2019-01-12 Fix light behaviour, increment person timeout
2019-08-11 trying some c++ libraries
2019-08-15 added upload.py
2019-08-31 use bathroom brightness sensor for hallway light control
2019-08-31 allow float config values
2019-08-31 allow upload tool to be killed by ctrl+c
2019-08-31 allow dimmer to be configured from other modules
2019-08-31 Forgot to commit BathroomStatus
2019-08-31 Add boiler node (WIP)
    including PID controller and obis listener
2019-09-01 Fix PID, add some debug
2019-09-02 Boiler control based on 1.8.0/2.8.0 power
2019-09-02 broadcast boiler status
2019-09-10 Boiler status receiver, max temperature
2019-09-10 different target power regulation
2019-09-14 decrease light during low-light conditions
2019-09-15 Add forgotten headers
2019-09-15 Clear bootloader commands on application entry
2019-09-15 Disable boiler debug
2019-09-15 add boiler status dsdl
2019-10-03 enable bme280 for boiler nodes
2019-10-31 Increase night brightness, fix timing
2019-11-03 mini pcb v2
2019-11-03 Boiler min temperature
2019-11-05 Improve 230V isolation and mounting spcae
2019-11-05 hub pcb
2019-11-17 Add bootloader flash readme
2019-11-17 I controller for flow temperature
2019-11-17 update v2pcb
2019-11-17 use newer openocd interface name
2019-11-17 Add bootloader flash script
2019-11-17 remove typo
2019-11-17 add some practical housebus software readme
2019-11-23 Add reasonable vscode c extension config
2019-11-23 Add missing files for pcbs
2019-11-23 Add image
2019-11-23 SPI & template for rfiddoor
2019-11-24 Add mfrc522 driver
2019-11-24 Fix using S function in non-interrupt context
2019-11-28 WIP password exchange
2019-12-21 add k22 hallway light
2020-05-31 remove unused current_power
2020-05-31 add boiler target temperature
2020-06-06 add shebang
2020-06-06 remove source file reference from generated dsdl files
2020-06-06 add motion sensor status
2020-06-06 update motion dsdl
2020-06-06 remove debug print
2020-06-18 hallway light: detect motion sensor level, not edge
2021-01-11 extend chibios systime by a few years for reporting
2021-01-11 limit flow deviation integral, use exponential algorithm
2021-02-10 fix slope key reading
2023-03-06 fix bathroom annoyances
2023-08-27 ignore door open status
